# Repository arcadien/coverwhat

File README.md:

# Hack - The game

Hack is a infrared based game, where players uses advanced gameplay to win. 
Rather than just having a player concept, many types and active objects will be added:

* healer player
* DPS player
* Support player
* Respawn point
* ... and more 

The code base targets high quality level and must keep a very high test coverage.
To ensure great behavior of hardware, testing automated scenario will be possible.

# Links
We rely on other open source projects, which are:
* [CMake](https://cmake.org/)
* [cmake-avr](https://github.com/mkleemann/cmake-avr)
* [iremote](https://github.com/z3t0/Arduino-IRremote)
* [Low-Power](https://github.com/rocketscream/Low-Power)
* [ssd1306](https://github.com/lexus2k/ssd1306)
* [Unity](https://www.throwtheswitch.org/unity)

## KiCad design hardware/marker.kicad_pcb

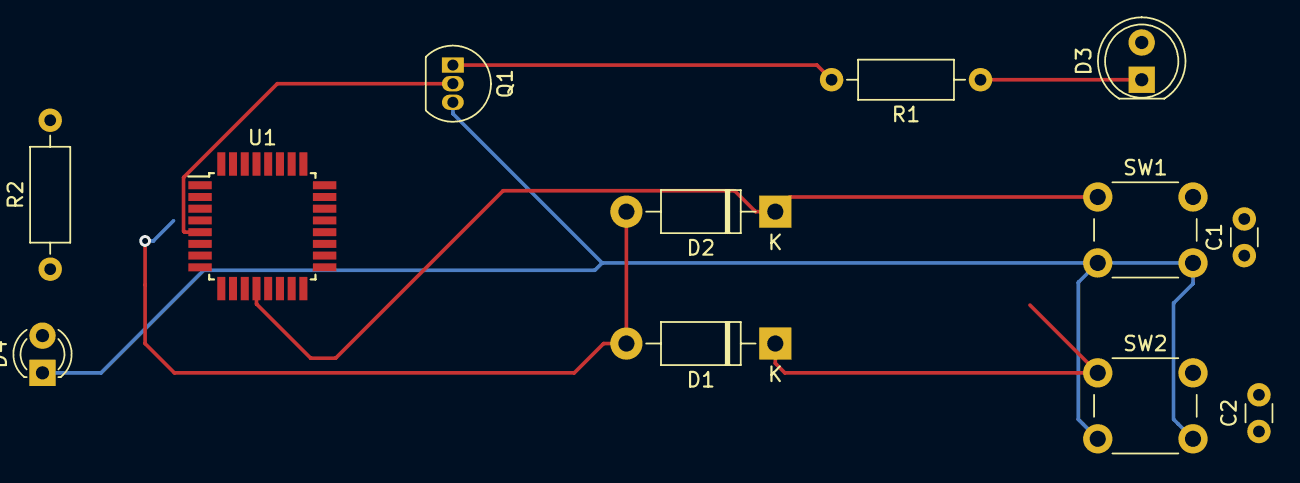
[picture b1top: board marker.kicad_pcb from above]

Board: 2 copper layers, 12 parts (0 on the bottom side), 10 nets.

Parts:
C1, C2: C; C_Disc_D3.0mm_W1.6mm_P2.50mm
D1, D2: 1N4004; D_DO-41_SOD81_P10.16mm_Horizontal
D3: SFH4546; LED_D5.0mm_IRGrey
D4: LED; LED_D3.0mm
Q1: BS170; TO-92_Inline
R1, R2: R; R_Axial_DIN0207_L6.3mm_D2.5mm_P10.16mm_Horizontal
SW1, SW2: SW_Push; SW_PUSH_6mm_H4.3mm
U1: ATmega328P-PU; TQFP-32_7x7mm_P0.8mm

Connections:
GND: C1.1, C2.1, D4.1, Q1.3, SW1.2, SW2.2, U1.8, U1.22
unnamed: C1.2, D2.1, SW1.1, U1.12
unnamed: C2.2, D1.1, SW2.1, U1.11
unnamed: D1.2, D2.2, U1.4
unnamed: D3.1, R1.1
unnamed: D4.2, R2.1
unnamed: Q1.1, R1.2
unnamed: Q1.2, U1.5
unnamed: R2.2, U1.19
VCC: D3.2, U1.7, U1.20, U1.21

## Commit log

2019-09-06 Initial commit
    * base hardware for marker
    * intial implementation for marker and player
2019-09-08 feat: Implement CMake configuration
    Use CMake so that project can be built on a PC for development and
    testing purpose. Also allow to build for AVR as it is the target
    platform.
2019-09-08 Feat: Initial commit of Hardware interface
2019-09-09 feat: Implement sleepMs function in simulation HW
    * Create a Hardware templated class, which uses a hardware
    implementation as template class. This allow to manipulate several
    hardware implementation without inheritance (and thus avoid virual call
    overhead).
    The first implementation of hardware is a simulated one, for PC hosts
    and testing purpose.
2019-09-09 typo: retab file
2019-09-09 chore(git): exclude build directory
2019-09-09 Fix: don't use mainWrapper file
2019-09-10 Fix: Fix compilation for AVR
2019-09-10 fix: remove useless test
2019-09-11 Fix: fix software build (ie not AVR build)
2019-09-11 Feat: Add Travis.ci configuration file
2019-09-11 feat: Better separation between API and implementations
2019-09-11 fix: Use library 'log' only with CLang
2019-09-11 fix: Use init script for AVR target CMake
2019-09-11 Fix: Fix compilation for AVR target
2019-09-11 Fix: Fix compilation for AVR target
    * Various fixes in CMake scripts
    * Add `arduino-core` package to AVR build environment
2019-09-11 fix: Use init script for AVR target CMake (#2)
    * Various fixes in CMake scripts
    * Add `arduino-core` package to AVR build environment
2019-09-11 chore: More isolation of AVR third party libraries
2019-09-18 feat: Add a script for code linting (clang-format)
2019-09-18 feat: Move C++ source code to sub directory
    * To enhance clarity of project, source code moves to a sub directory.
2019-09-18 feat: Move C++ source code to sub directory (#4)
    * To enhance clarity of project, source code moves to a sub directory.
2019-10-02 feat: Initial version of roadmap
2019-10-02 doc: refine v1.0
2019-10-09 Add Coveralls badge
2019-10-11 feat(action): First implementation
2019-10-11 docs: Add CHANGELOG and update Readme
2019-10-11 refactor: Cleanup in Action and Actor
2019-10-11 test(weapon): Add initial unit test
2019-10-11 feat(doc): Provide Gherkin definition of scenario
    This first Gherkin file will describe the initial validation
    scenario for API v1.
2019-10-11 feat(weapon): Add Vampire
2019-10-11 test(Vampire): add unit test
2019-10-11 chore(build): Do not use headers not available for AVR in API
2019-10-11 chore(build): Fix bootstrap script
2019-10-11 chore(build): Fix GCC build
2019-10-11 chore(tests): Output error on ctest failure
2019-10-11 chore(coverage): Implement coverage data collection
2019-10-11 chore(structure): Changed CMakeLists.txt
2019-10-11 chore(lint): code linting
2019-10-11 feat(transport): initial implementation of Transport
2019-10-11 refactor: Better split of code
    * Created h and cpp files for classes which was inside API headers for
    now.
2019-10-11 fix(Vampire): Fix unit test
2019-10-11 chore(build): Fix build for AVR target
2019-10-11 chore(third-party): Updated Unity
2019-10-11 chore(build): Don't use -WError for now for AVR
2019-10-11 chore(build): fix GCC warning
2019-10-11 feat(hardware): Add main clock to hardware and Simulator
2019-10-11 fix(typo): We talk about Transport, not Protocol
2019-10-11 chore(build): Do not include simulator code in AVR build
2019-10-11 chore(Readme): Update badges
2019-10-14 chore(apidoc): enhance Doxygen
2019-10-14 chore(Readme): Fix short project description
2019-10-17 fix: Stop() hardware before test end
    * The Simulator was not stopped in one of its tests, causing occasional
    segfaults
2019-10-17 fix(#10) : separate ATMega and Simulator tests
2019-10-17 Fix IHardware test on ATMega328p
2019-10-17 Remove non-avr includes
2019-10-17 Fix ATMega328p hardware class name
2019-10-17 chore(coverage): Better Codecov support
    * Usage of Cobertura report
    * upload PC coverage code
2019-10-17 doc(Readme): Update badges
2019-10-18 chore(tests) : Add unit test for DummyTransport
2019-10-18 chore(tests): Add unit tests for Entity
2019-10-18 feat(simulator) : Add methods for prim/sec action trigger
2019-10-18 chore(build) : remove coverall.io support
2019-10-18 chore(build): cleaner management of coverage build
2019-10-18 chore(coverage) : Prevent GCC inline code in coverage mode
2019-10-18 chore(build): Do coverage in debug mode to avoid optimization
2019-10-18 fix() : Better implementation of simulated timer
2019-10-21 feat: Add more Action types
2019-10-21 feat: Add new 'None' Entity tag
2019-10-21 feat: Allow empty constuctor for Action
2019-10-21 feat: Add new class Timer
2019-10-21 feat: Add new UI concept
2019-10-21 refactor: enhancement of global Action system
2019-10-21 chore(build): Fix AVR build (changed filename)
2019-10-21 chore(build): Fix AVR build
    * Software implementation of transport does not compile with gcc-avr
2019-10-21 chore(Transport): Simplify unfinished implementation
2019-10-21 chore(build): re-enable software transport for AVR
2019-10-22 chore: Change folder structure
2019-10-22 test: Add test for Simulator
2019-10-22 chore(build): Fix Linux build after structure changes
2019-10-22 test: Add tests for DummyTransport
2019-10-23 chore(coverage): Fix coverage build for GCC/Linux
2019-10-24 chore(Simulator): Fix threading issues
2019-10-24 chore(Atmega328p): Align implementation on IHardware
2019-10-25 tests(Action): Add missing tests for Action types
2019-10-25 feat(tools): Add new RGBColor class and update AVR code
2019-10-26 chore(coverage): Raise test coverage of RGBColor
2019-10-26 refactor: implement and use BluetoothElectronic UI
    SAVEPOINT
2019-10-26 chore: use colors for Unity (native)
2019-10-27 feat(Action): Add IAction, interface for actions
2019-10-28 chore: Remove useless include
2019-10-28 fix(Action): Fix a bug in Action processing
    * When a DAMAGE action was lowering a value below zero, an overflow was causing a bug.
    When the bug occured, the value, supposed to be zero, was instead very high.
2019-10-28 feat(ConsolePlayer): Add a new Player implementation for testing
    ConsolePlayer is implemented to allow testing of Koth API on a PC with a simulated device.
2019-10-28 feat: Create dedicated object for Action creation from string
    * Create new factory
    * Allow ConsoleUi to be tested
2019-10-28 refactor: Don't use string or regex in generic code
2019-10-28 fix: Crash when thread does not finishes at time
2019-10-29 chore(license): Add license header in source files
2019-10-29 chore(licenses): more licence headers (cmake, scripts)
2019-10-31 feat: Initial support of Team
2019-11-03 refactor: simpler access for health, the only entity for now
2019-11-03 tests: enhance ConsoleUi tests
2019-11-05 fix: MSVC warnings and compilers specific options
2019-11-05 chore: Allow cross-compilation to AVR on Windows hosts
2019-11-05 chore: Fix Windows cross build
2019-11-05 Fix Linux cross build
2019-11-05 chore: New submodule for SSD1306 oled screen
2019-11-05 chore: Fix cross build Linux/Windows
2019-11-06 efactor: better management of initial health
2019-11-06 test: ensure a Player can resurrect
2019-11-07 chore: Fix submodule for SSD1306 lib
2019-11-08 chore: Documentation update
2019-11-08 chore: rename 'Koth' to 'Hack'
2019-11-09 refactor: Allow representation of Action on 32 bits
2019-11-15 fix(#14): new millisecond counting implem. in simulator
    * New implementation for `hardware::Simulator::delayMs()`
    * Better stability of tests relying on time
2019-11-15 chore: Ignore VS Code files
2019-11-27 feat: New player implementation
    * Using Hack infrastructure
    * Implementation of a SSD1306 display in place of RGB led
2019-11-27 chore(build): Fix usage of Arduino and SSD1306 lib
2019-11-27 typo fix
2019-11-27 doc: Update readme
2019-11-28 chore(build): add small script for AVR file size record
2020-01-29 Move code to PlatformIO-compatible structure
2020-01-29 chore: preliminary PlatformIO support
